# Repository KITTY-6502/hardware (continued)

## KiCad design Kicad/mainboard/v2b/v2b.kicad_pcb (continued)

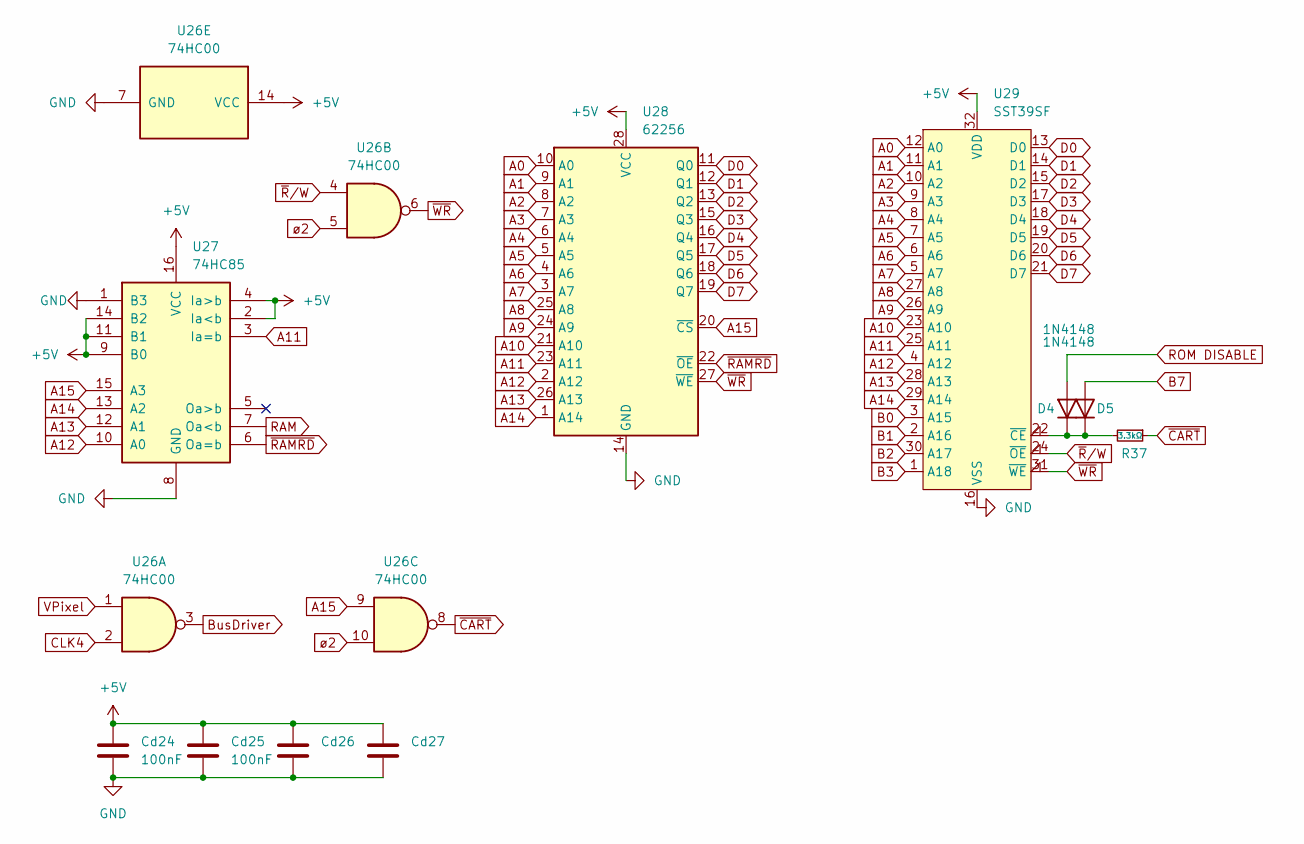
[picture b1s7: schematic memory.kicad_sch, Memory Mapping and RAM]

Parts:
Cd24, Cd25, Cd26, Cd27: 100nF; C_Disc_D3.0mm_W1.6mm_P2.50mm
D4, D5: 1N4148; D_DO-34_SOD68_P7.62mm_Horizontal
R37: 3.3kΩ; R_Horizontal
U26: 74HC00; DIP-14_W7.62mm_Socket_LongPads_TWEAK
U27: 74HC85; DIP-16_W7.62mm_Socket_LongPads_TWEAK
U28: 62256; DIP-28_W15.24mm_Socket_LongPads_TWEAK
U29: SST39SF; PLCC-32_THT-Socket_TWEAK

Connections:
+5V: Cd24.1, Cd25.1, Cd26.1, Cd27.1, U26.14 (VCC), U27.2 (Ia<b), U27.4 (Ia>b), U27.9 (B0), U27.11 (B1), U27.14 (B2), U27.16 (VCC), U28.28 (VCC), U29.32 (VDD); also elsewhere on the board
A0: U28.10 (A0), U29.12 (A0); also elsewhere on the board
A1: U28.9 (A1), U29.11 (A1); also elsewhere on the board
A2: U28.8 (A2), U29.10 (A2); also elsewhere on the board
A3: U28.7 (A3), U29.9 (A3); also elsewhere on the board
A4: U28.6 (A4), U29.8 (A4); also elsewhere on the board
A5: U28.5 (A5), U29.7 (A5); also elsewhere on the board
A6: U28.4 (A6), U29.6 (A6); also elsewhere on the board
A7: U28.3 (A7), U29.5 (A7); also elsewhere on the board
A8: U28.25 (A8), U29.27 (A8); also elsewhere on the board
A9: U28.24 (A9), U29.26 (A9); also elsewhere on the board
A10: U28.21 (A10), U29.23 (A10); also elsewhere on the board
A11: U27.3 (Ia=b), U28.23 (A11), U29.25 (A11); also elsewhere on the board
A12: U27.10 (A0), U28.2 (A12), U29.4 (A12); also elsewhere on the board
A13: U27.12 (A1), U28.26 (A13), U29.28 (A13); also elsewhere on the board
A14: U27.13 (A2), U28.1 (A14), U29.29 (A14); also elsewhere on the board
A15: U26.9, U27.15 (A3), U28.20 (~CS); also elsewhere on the board
B0: U29.3 (A15); also elsewhere on the board
B1: U29.2 (A16); also elsewhere on the board
B2: U29.30 (A17); also elsewhere on the board
B3: U29.1 (A18); also elsewhere on the board
B7: D5.2 (A); also elsewhere on the board
BusDriver: U26.3; also elsewhere on the board
CLK2: U26.5, U26.10; also elsewhere on the board
CLK4: U26.2; also elsewhere on the board
D0: U28.11 (Q0), U29.13 (D0); also elsewhere on the board
D1: U28.12 (Q1), U29.14 (D1); also elsewhere on the board
D2: U28.13 (Q2), U29.15 (D2); also elsewhere on the board
D3: U28.15 (Q3), U29.17 (D3); also elsewhere on the board
D4: U28.16 (Q4), U29.18 (D4); also elsewhere on the board
D5: U28.17 (Q5), U29.19 (D5); also elsewhere on the board
D6: U28.18 (Q6), U29.20 (D6); also elsewhere on the board
D7: U28.19 (Q7), U29.21 (D7); also elsewhere on the board
GND: Cd24.2, Cd25.2, Cd26.2, Cd27.2, U26.7 (GND), U27.1 (B3), U27.8 (GND), U28.14 (GND), U29.16 (VSS); also elsewhere on the board
unnamed: D4.1 (K), D5.1 (K), R37.2, U29.22 (~CE)
RAM: U27.7 (Oa<b); also elsewhere on the board
ROM DISABLE: D4.2 (A); also elsewhere on the board
VPixel: U26.1; also elsewhere on the board
~CART: R37.1, U26.8; also elsewhere on the board
~RAMRD: U27.6 (Oa=b), U28.22 (~OE); also elsewhere on the board
~R/W: U26.4, U29.24 (~OE); also elsewhere on the board
~WR: U26.6, U28.27 (~WE), U29.31 (~WE); also elsewhere on the board

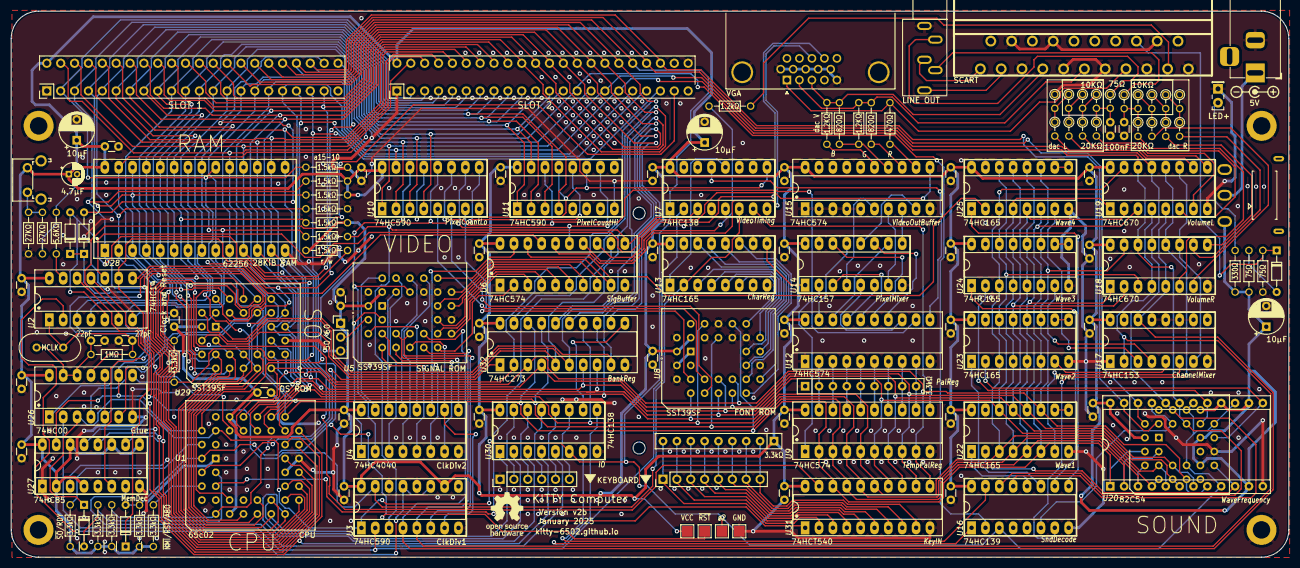
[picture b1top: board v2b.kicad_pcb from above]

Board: 2 copper layers, 234.0 x 100.0 mm, 146 parts (0 on the bottom side), 199 nets.

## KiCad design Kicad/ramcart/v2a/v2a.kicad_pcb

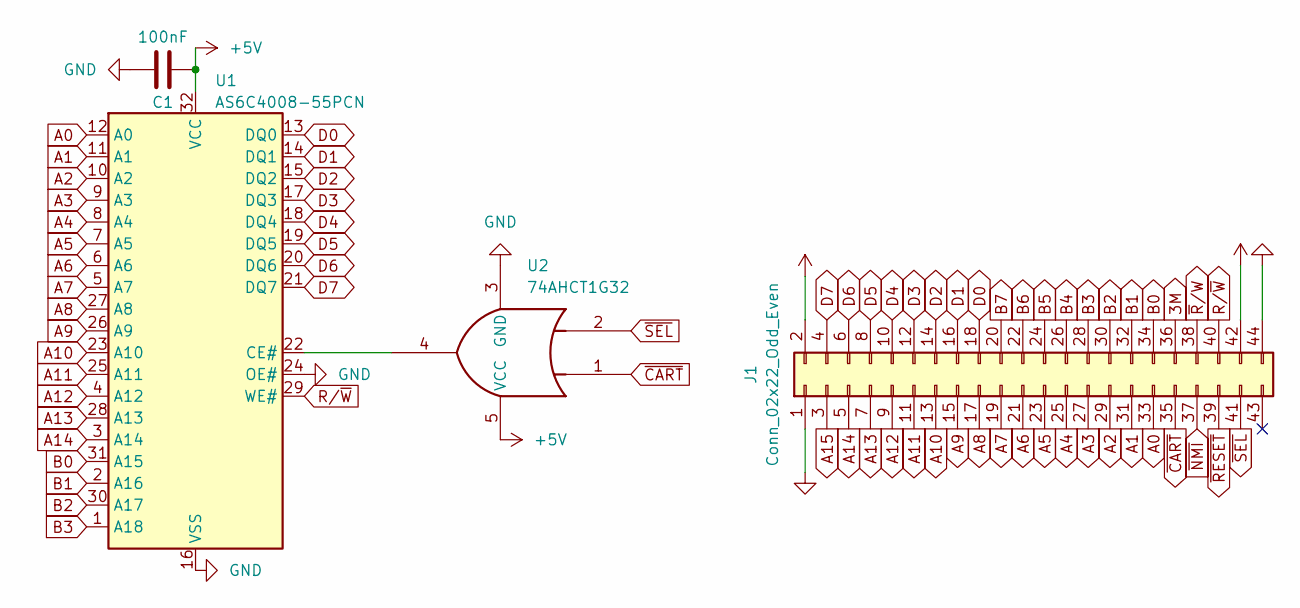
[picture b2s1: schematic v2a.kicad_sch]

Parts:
C1: 100nF; C_Disc_D3.0mm_W1.6mm_P2.50mm
J1: Conn_02x22_Odd_Even; KITTY_Cart_Edge
U1: AS6C4008-55PCN; DIP-32_W15.24mm_Socket_LongPads
U2: 74AHCT1G32; SOT-23-5

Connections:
3M: J1.36
+5V: C1.2, J1.2, J1.42, U1.32 (VCC), U2.5 (VCC)
A0: J1.33, U1.12 (A0)
A1: J1.31, U1.11 (A1)
A2: J1.29, U1.10 (A2)
A3: J1.27, U1.9 (A3)
A4: J1.25, U1.8 (A4)
A5: J1.23, U1.7 (A5)
A6: J1.21, U1.6 (A6)
A7: J1.19, U1.5 (A7)
A8: J1.17, U1.27 (A8)
A9: J1.15, U1.26 (A9)
A10: J1.13, U1.23 (A10)
A11: J1.11, U1.25 (A11)
A12: J1.9, U1.4 (A12)
A13: J1.7, U1.28 (A13)
A14: J1.5, U1.3 (A14)
A15: J1.3
B0: J1.34, U1.31 (A15)
B1: J1.32, U1.2 (A16)
B2: J1.30, U1.30 (A17)
B3: J1.28, U1.1 (A18)
B4: J1.26
B5: J1.24
B6: J1.22
B7: J1.20
D0: J1.18, U1.13 (DQ0)
D1: J1.16, U1.14 (DQ1)
D2: J1.14, U1.15 (DQ2)
D3: J1.12, U1.17 (DQ3)
D4: J1.10, U1.18 (DQ4)
D5: J1.8, U1.19 (DQ5)
D6: J1.6, U1.20 (DQ6)
D7: J1.4, U1.21 (DQ7)
GND: C1.1, J1.1, J1.44, U1.16 (VSS), U1.24 (OE#), U2.3 (GND)
unnamed: U1.22 (CE#), U2.4
R/~W: J1.40, U1.29 (WE#)
~CART: J1.35, U2.1
~NMI: J1.37
~RESET: J1.39
~R/W: J1.38
~SEL: J1.41, U2.2

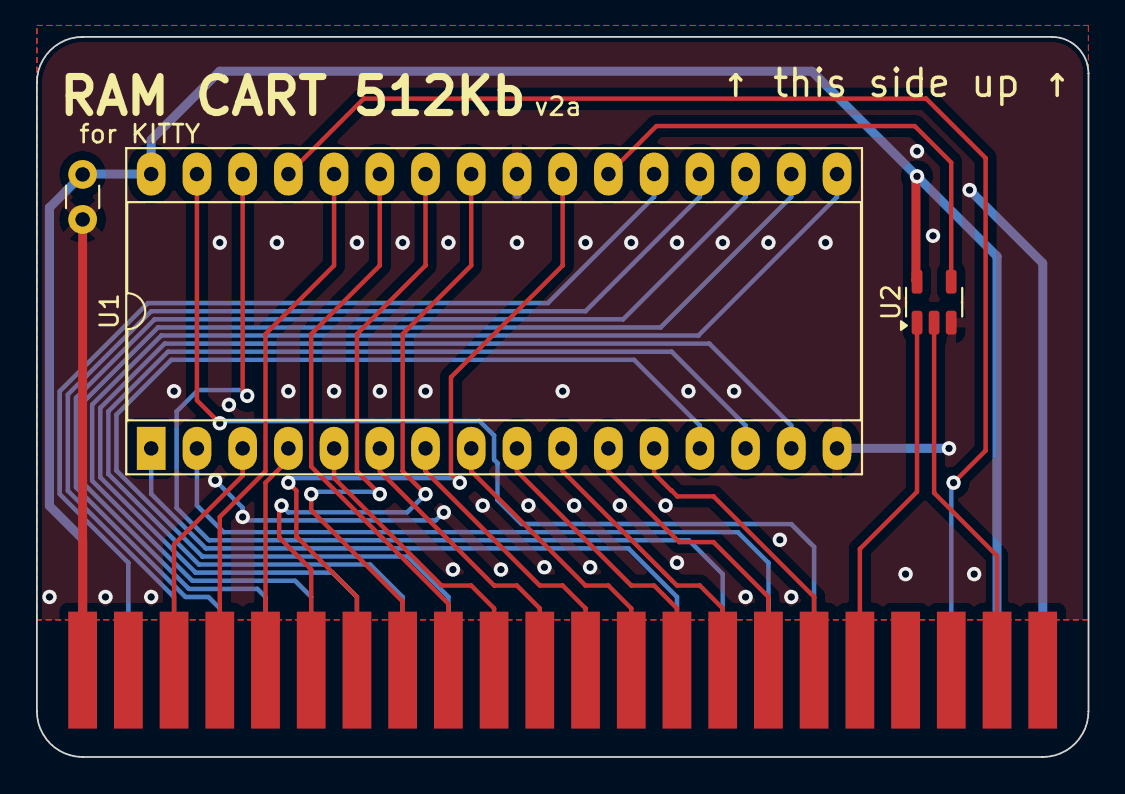
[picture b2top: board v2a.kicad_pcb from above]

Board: 2 copper layers, 58.4 x 40.0 mm, 4 parts (0 on the bottom side), 33 nets.

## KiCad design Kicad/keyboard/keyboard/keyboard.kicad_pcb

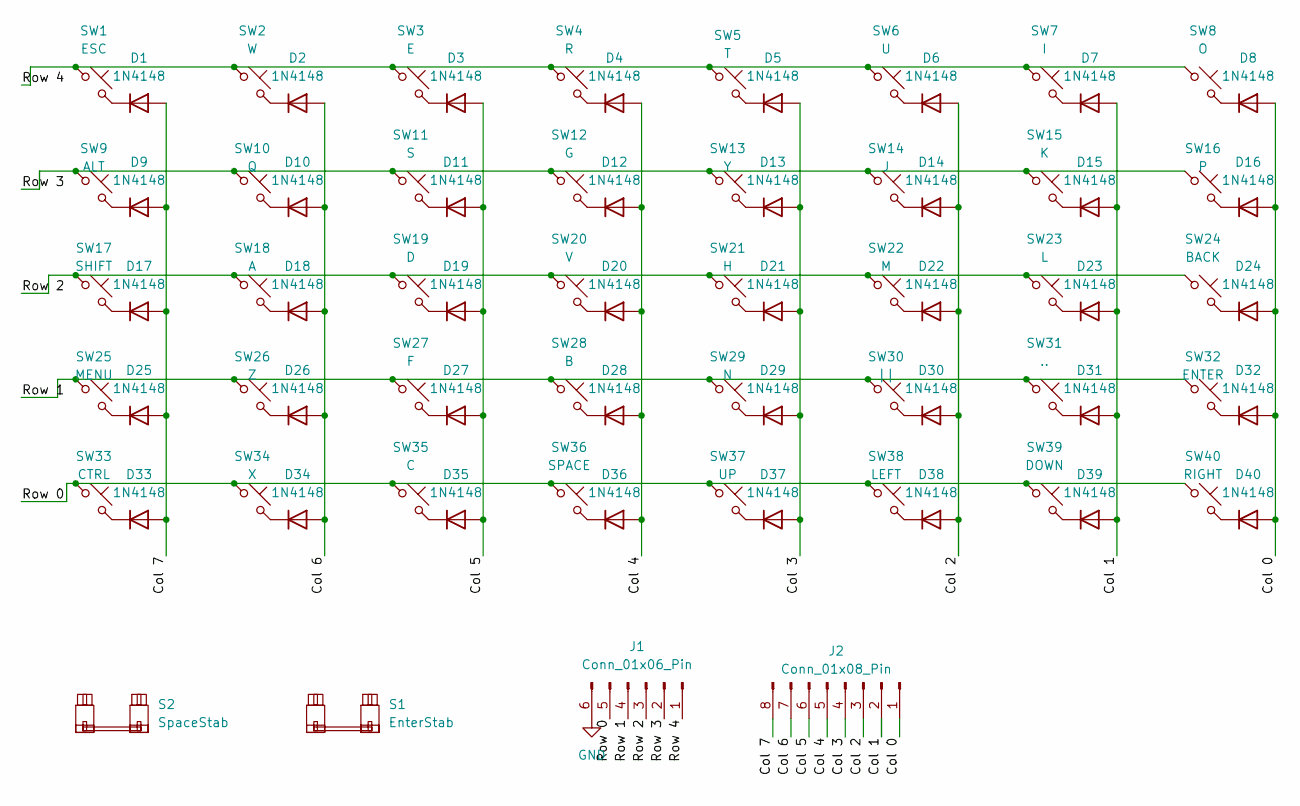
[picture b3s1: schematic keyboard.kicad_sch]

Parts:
D1, D2, D3, D4, D5, D6, D7, D8, D9, D10, D11, D12, D13, D14, D15, D16, D17, D18, D19, D20, D21, D22, D23, D24, D25, D26, D27, D28, D29, D30, D31, D32, D33, D34, D35, D36, D37, D38, D39, D40: 1N4148; D_DO-35_SOD27_P7.62mm_Horizontal
J1: Conn_01x06_Pin; PinHeader_1x06_P2.54mm_Vertical
J2: Conn_01x08_Pin; PinHeader_1x08_P2.54mm_Vertical
S1: EnterStab; ks27_2u_pcb_cherry_plate_stab
S2: SpaceStab; ks26_6.25u_pcb_cherry_plate
SW1: ESC; SW_Redragon_LowProfile_PCB_1.00u
SW2: W; SW_Redragon_LowProfile_PCB_1.00u
SW3: E; SW_Redragon_LowProfile_PCB_1.00u
SW4: R; SW_Redragon_LowProfile_PCB_1.00u
SW5: T; SW_Redragon_LowProfile_PCB_1.00u
SW6: U; SW_Redragon_LowProfile_PCB_1.00u
SW7: I; SW_Redragon_LowProfile_PCB_1.00u
SW8: O; SW_Redragon_LowProfile_PCB_1.00u
SW9: ALT; SW_Redragon_LowProfile_PCB_1.25u
SW10: Q; SW_Redragon_LowProfile_PCB_1.00u
SW11: S; SW_Redragon_LowProfile_PCB_1.00u
SW12: G; SW_Redragon_LowProfile_PCB_1.00u
SW13: Y; SW_Redragon_LowProfile_PCB_1.00u
SW14: J; SW_Redragon_LowProfile_PCB_1.00u
SW15: K; SW_Redragon_LowProfile_PCB_1.00u
SW16: P; SW_Redragon_LowProfile_PCB_1.00u
SW17: SHIFT; SW_Redragon_LowProfile_PCB_1.75u
SW18: A; SW_Redragon_LowProfile_PCB_1.00u
SW19: D; SW_Redragon_LowProfile_PCB_1.00u
SW20: V; SW_Redragon_LowProfile_PCB_1.00u
SW21: H; SW_Redragon_LowProfile_PCB_1.00u
SW22: M; SW_Redragon_LowProfile_PCB_1.00u
SW23: L; SW_Redragon_LowProfile_PCB_1.00u
SW24: BACK; SW_Redragon_LowProfile_PCB_1.25u
SW25: MENU; SW_Redragon_LowProfile_PCB_1.50u
SW26: Z; SW_Redragon_LowProfile_PCB_1.00u
SW27: F; SW_Redragon_LowProfile_PCB_1.00u
SW28: B; SW_Redragon_LowProfile_PCB_1.00u
SW29: N; SW_Redragon_LowProfile_PCB_1.00u
SW30: ||; SW_Redragon_LowProfile_PCB_1.50u
SW31: ..; SW_Redragon_LowProfile_PCB_1.00u
SW32: ENTER; SW_Redragon_LowProfile_PCB_2.00u
SW33: CTRL; SW_Redragon_LowProfile_PCB_1.50u
SW34: X; SW_Redragon_LowProfile_PCB_1.00u
SW35: C; SW_Redragon_LowProfile_PCB_1.00u
SW36: SPACE; SW_Redragon_LowProfile_PCB_6.25u
SW37: UP; SW_Redragon_LowProfile_PCB_1.00u
SW38: LEFT; SW_Redragon_LowProfile_PCB_1.00u
SW39: DOWN; SW_Redragon_LowProfile_PCB_1.00u
SW40: RIGHT; SW_Redragon_LowProfile_PCB_1.00u

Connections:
/Col 0: D8.2 (A), D16.2 (A), D24.2 (A), D32.2 (A), D40.2 (A), J2.1
/Col 1: D7.2 (A), D15.2 (A), D23.2 (A), D31.2 (A), D39.2 (A), J2.2
/Col 2: D6.2 (A), D14.2 (A), D22.2 (A), D30.2 (A), D38.2 (A), J2.3
/Col 3: D5.2 (A), D13.2 (A), D21.2 (A), D29.2 (A), D37.2 (A), J2.4
/Col 4: D4.2 (A), D12.2 (A), D20.2 (A), D28.2 (A), D36.2 (A), J2.5
/Col 5: D3.2 (A), D11.2 (A), D19.2 (A), D27.2 (A), D35.2 (A), J2.6
/Col 6: D2.2 (A), D10.2 (A), D18.2 (A), D26.2 (A), D34.2 (A), J2.7
/Col 7: D1.2 (A), D9.2 (A), D17.2 (A), D25.2 (A), D33.2 (A), J2.8
/Row 0: J1.5, SW33.1, SW34.1, SW35.1, SW36.1, SW37.1, SW38.1, SW39.1, SW40.1
/Row 1: J1.4, SW25.1, SW26.1, SW27.1, SW28.1, SW29.1, SW30.1, SW31.1, SW32.1
/Row 2: J1.3, SW17.1, SW18.1, SW19.1, SW20.1, SW21.1, SW22.1, SW23.1, SW24.1
/Row 3: J1.2, SW9.1, SW10.1, SW11.1, SW12.1, SW13.1, SW14.1, SW15.1, SW16.1
/Row 4: J1.1, SW1.1, SW2.1, SW3.1, SW4.1, SW5.1, SW6.1, SW7.1, SW8.1
GND: J1.6
unnamed: D1.1 (K), SW1.2
unnamed: D2.1 (K), SW2.2
unnamed: D3.1 (K), SW3.2
unnamed: D4.1 (K), SW4.2
unnamed: D5.1 (K), SW5.2
unnamed: D6.1 (K), SW6.2
unnamed: D7.1 (K), SW7.2
unnamed: D8.1 (K), SW8.2
unnamed: D9.1 (K), SW9.2
unnamed: D10.1 (K), SW10.2
unnamed: D11.1 (K), SW11.2
unnamed: D12.1 (K), SW12.2
unnamed: D13.1 (K), SW13.2
unnamed: D14.1 (K), SW14.2
unnamed: D15.1 (K), SW15.2
unnamed: D16.1 (K), SW16.2
unnamed: D17.1 (K), SW17.2
unnamed: D18.1 (K), SW18.2
unnamed: D19.1 (K), SW19.2
unnamed: D20.1 (K), SW20.2
unnamed: D21.1 (K), SW21.2
unnamed: D22.1 (K), SW22.2
unnamed: D23.1 (K), SW23.2
unnamed: D24.1 (K), SW24.2
unnamed: D25.1 (K), SW25.2
unnamed: D26.1 (K), SW26.2
unnamed: D27.1 (K), SW27.2
unnamed: D28.1 (K), SW28.2
unnamed: D29.1 (K), SW29.2
unnamed: D30.1 (K), SW30.2
unnamed: D31.1 (K), SW31.2
unnamed: D32.1 (K), SW32.2
unnamed: D33.1 (K), SW33.2
unnamed: D34.1 (K), SW34.2
unnamed: D35.1 (K), SW35.2
unnamed: D36.1 (K), SW36.2
unnamed: D37.1 (K), SW37.2
unnamed: D38.1 (K), SW38.2
unnamed: D39.1 (K), SW39.2
unnamed: D40.1 (K), SW40.2

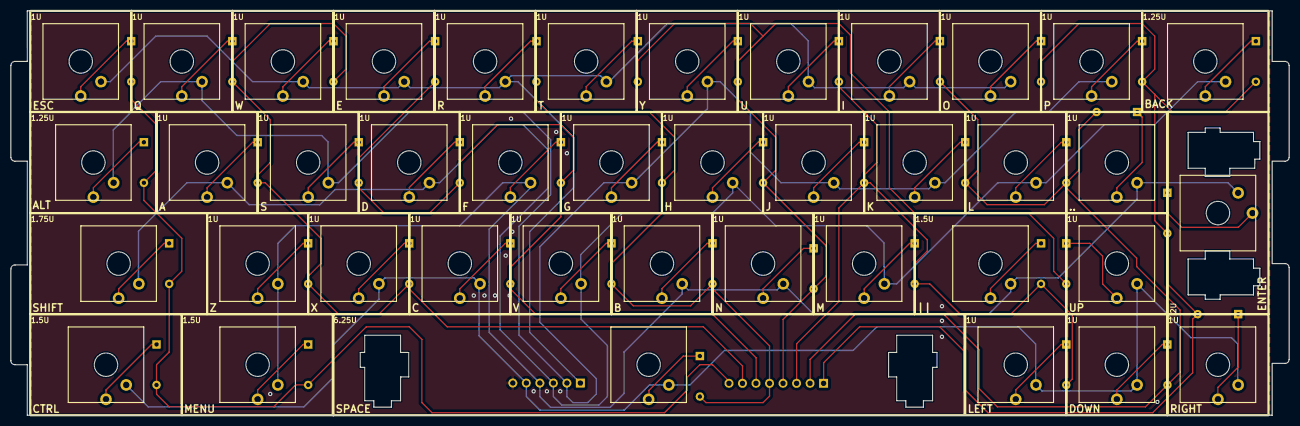
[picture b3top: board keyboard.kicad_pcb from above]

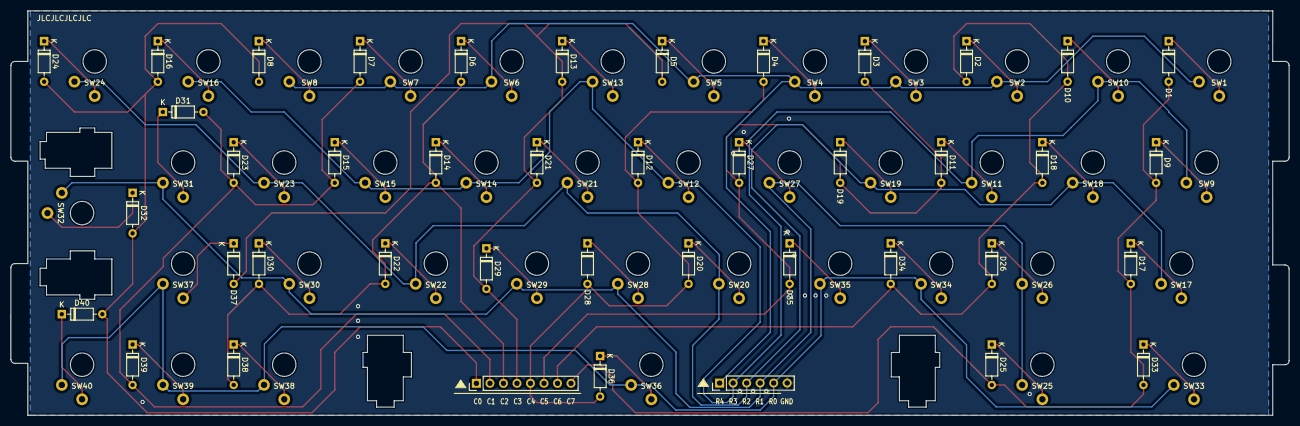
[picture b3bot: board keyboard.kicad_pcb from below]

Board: 2 copper layers, 240.2 x 76.0 mm, 84 parts (42 on the bottom side), 53 nets.

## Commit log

2024-01-18 update kicad files
2024-01-18 docs stub for serial,rom,ram carts
2024-04-26 big v1b commit
2024-06-02 v2a update
2024-06-02 add schematic
2024-06-04 docs update
2024-07-25 Update board files
2025-01-18 Updated pcb files and python scripts
